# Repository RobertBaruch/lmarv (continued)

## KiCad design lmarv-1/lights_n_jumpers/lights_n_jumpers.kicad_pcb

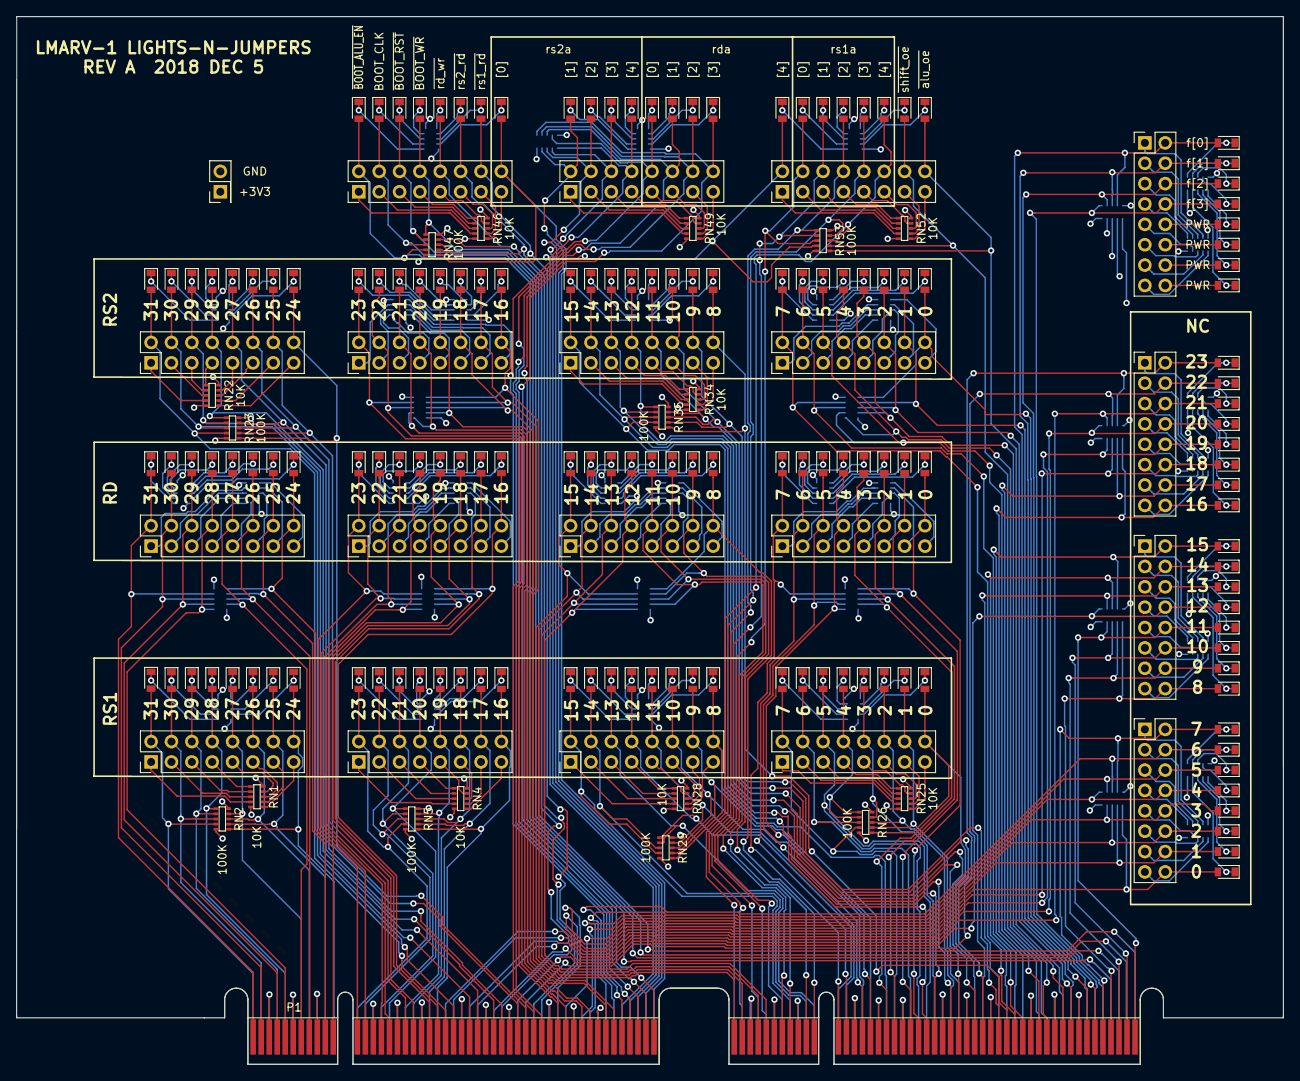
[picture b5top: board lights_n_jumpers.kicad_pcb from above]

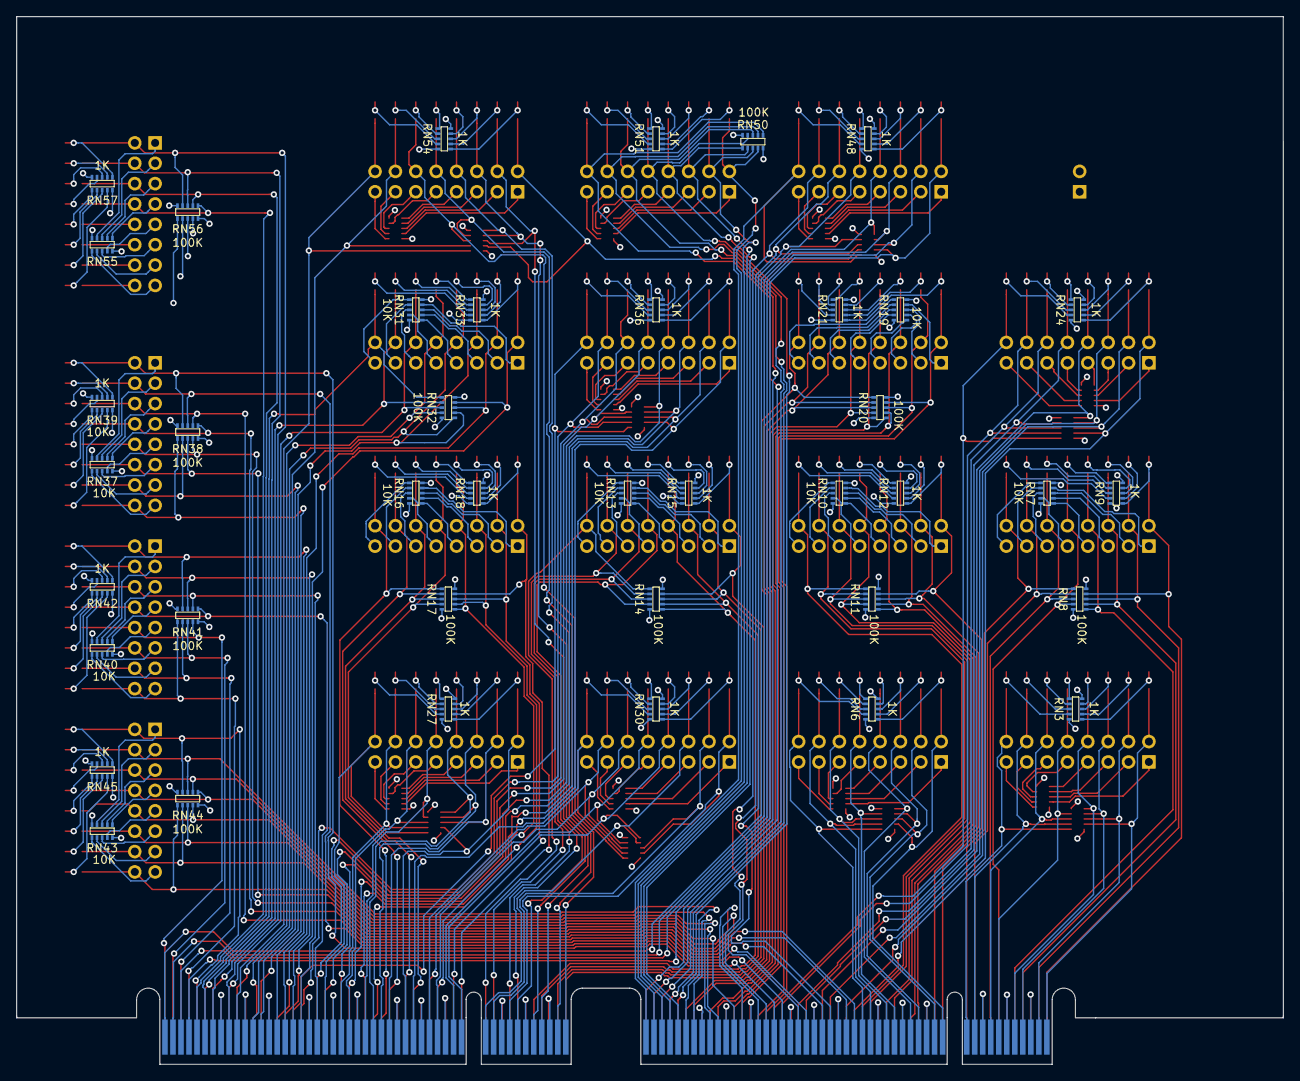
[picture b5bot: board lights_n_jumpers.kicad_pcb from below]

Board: 4 copper layers, 158.0 x 130.7 mm, 230 parts (40 on the bottom side), 454 nets.

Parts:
D1, D2, D3, D4, D5, D6, D7, D8, D9, D10, D11, D12, D13, D14, D15, D16, D17, D18, D19, D20, D21, D22, D23, D24, D25, D26, D27, D28, D29, D30, D31, D32, D33, D34, D35, D36, D37, D38, D39, D40, D41, D42, D43, D44, D45, D46, D47, D48, D49, D50, D51, D52, D53, D54, D55, D56, D57, D58, D59, D60, D61, D62, D63, D64, D65, D66, D67, D68, D69, D70, D71, D72, D73, D74, D75, D76, D77, D78, D79, D80, D81, D82, D83, D84, D85, D86, D87, D88, D89, D90, D91, D92, D93, D94, D95, D96, D97, D98, D99, D100, D101, D102, D103, D104, D105, D106, D107, D108, D109, D110, D111, D112, D113, D114, D115, D116, D117, D118, D119, D120, D121, D122, D123, D124, D125, D126, D127, D128, D129, D130, D131, D132, D133, D134, D135, D136, D137, D138, D139, D140, D141, D142, D143, D144, D145, D146, D147, D148, D149, D150, D151, D152: APTD2012LSURCK; D_0805_Wide
J1, J2, J3, J4, J5, J6, J7, J8, J10, J11, J12, J13, J14, J15, J16, J17, J18, J19, J20: Conn_02x08_Odd_Even; PinHeader_2x08_P2.54mm_Vertical
J9: Conn_01x02; PinHeader_2x01_P2.54mm_Vertical
P1: dual-pcie-cardedge_split; PCI-EXPRESS
RN1, RN4, RN7, RN10, RN13, RN16, RN19, RN22, RN25, RN28, RN31, RN34, RN37, RN40, RN43, RN46, RN49, RN52, RN55: 10k; CAY17
RN2, RN5, RN8, RN11, RN14, RN17, RN20, RN23, RN26, RN29, RN32, RN35, RN38, RN41, RN44, RN47, RN50, RN53, RN56: 100k; CAY17
RN3, RN6, RN9, RN12, RN15, RN18, RN21, RN24, RN27, RN30, RN33, RN36, RN39, RN42, RN45, RN48, RN51, RN54, RN57: 1k; CAY17

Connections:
+3V3: D145.2, D146.2, D147.2, D148.2, J9.1, J20.10, J20.12, J20.14, J20.16, P1.6, P1.17, P1.28, P1.39, P1.55, P1.66, P1.77, P1.88, P1.104, P1.115, P1.126, P1.137, P1.153, P1.164, P1.175, P1.186, RN1.5, RN1.10, RN4.5, RN4.10, RN7.5, RN7.10, RN10.5, RN10.10, RN13.5, RN13.10, RN16.5, RN16.10, RN19.5, RN19.10, RN22.5, RN22.10, RN25.5, RN25.10, RN28.5, RN28.10, RN31.5, RN31.10, RN34.5, RN34.10, RN37.5, RN37.10, RN40.5, RN40.10, RN43.5, RN43.10, RN46.5, RN46.10, RN49.5, RN49.10, RN52.5, RN52.10, RN55.5, RN55.10, RN56.1, RN56.2, RN56.3, RN56.4
/BOOT_CLK: D127.2, J17.4, P1.194, RN47.8
/f[0]: D152.2, J20.2, P1.188, RN56.9
/f[1]: D151.2, J20.4, P1.190, RN56.8
/f[2]: D150.2, J20.6, P1.191, RN56.7
/f[3]: D149.2, J20.8, P1.192, RN56.6
/nc0: D113.2, J16.16, P1.133, RN44.1
/nc1: D114.2, J16.14, P1.135, RN44.2
/nc2: D115.2, J16.12, P1.136, RN44.3
/nc3: D116.2, J16.10, P1.138, RN44.4
/nc4: D117.2, J16.8, P1.139, RN44.6
/nc5: D118.2, J16.6, P1.141, RN44.7
/nc6: D119.2, J16.4, P1.142, RN44.8
/nc7: D120.2, J16.2, P1.94, RN44.9
/nc8: D105.2, J15.16, P1.95, RN41.1
/nc9: D106.2, J15.14, P1.96, RN41.2
/nc10: D107.2, J15.12, P1.97, RN41.3
/nc11: D108.2, J15.10, P1.98, RN41.4
/nc12: D109.2, J15.8, P1.177, RN41.6
/nc13: D110.2, J15.6, P1.179, RN41.7
/nc14: D111.2, J15.4, P1.180, RN41.8
/nc15: D112.2, J15.2, P1.181, RN41.9
/nc16: D97.2, J14.16, P1.182, RN38.1
/nc17: D98.2, J14.14, P1.184, RN38.2
/nc18: D99.2, J14.12, P1.121, RN38.3
/nc19: D100.2, J14.10, P1.122, RN38.4
/nc20: D101.2, J14.8, P1.125, RN38.6
/nc21: D102.2, J14.6, P1.127, RN38.7
/nc22: D103.2, J14.4, P1.130, RN38.8
/nc23: D104.2, J14.2, P1.131, RN38.9
/rd[0]: D41.2, J6.16, P1.71, RN17.1
/rd[1]: D42.2, J6.14, P1.70, RN17.2
/rd[2]: D43.2, J6.12, P1.68, RN17.3
/rd[3]: D44.2, J6.10, P1.67, RN17.4
/rd[4]: D45.2, J6.8, P1.65, RN17.6
/rd[5]: D46.2, J6.6, P1.64, RN17.7
/rd[6]: D47.2, J6.4, P1.62, RN17.8
/rd[7]: D48.2, J6.2, P1.61, RN17.9
/rd[8]: D33.2, J5.16, P1.60, RN14.1
/rd[9]: D34.2, J5.14, P1.59, RN14.2
/rd[10]: D35.2, J5.12, P1.57, RN14.3
/rd[11]: D36.2, J5.10, P1.56, RN14.4
/rd[12]: D37.2, J5.8, P1.54, RN14.6
/rd[13]: D38.2, J5.6, P1.53, RN14.7
/rd[14]: D39.2, J5.4, P1.51, RN14.8
/rd[15]: D40.2, J5.2, P1.50, RN14.9
/rd[16]: D25.2, J4.16, P1.22, RN11.1
/rd[17]: D26.2, J4.14, P1.21, RN11.2
/rd[18]: D27.2, J4.12, P1.19, RN11.3
/rd[19]: D28.2, J4.10, P1.18, RN11.4
/rd[20]: D29.2, J4.8, P1.16, RN11.6
/rd[21]: D30.2, J4.6, P1.15, RN11.7
/rd[22]: D31.2, J4.4, P1.13, RN11.8
/rd[23]: D32.2, J4.2, P1.12, RN11.9
/rd[24]: D17.2, J3.16, P1.11, RN8.1
/rd[25]: D18.2, J3.14, P1.10, RN8.2
/rd[26]: D19.2, J3.12, P1.8, RN8.3
/rd[27]: D20.2, J3.10, P1.7, RN8.4
/rd[28]: D21.2, J3.8, P1.5, RN8.6
/rd[29]: D22.2, J3.6, P1.4, RN8.7
/rd[30]: D23.2, J3.4, P1.2, RN8.8
/rd[31]: D24.2, J3.2, P1.1, RN8.9
/rda[0]: D132.2, J18.10, P1.45, RN50.4
/rda[1]: D131.2, J18.12, P1.46, RN50.3
/rda[2]: D130.2, J18.14, P1.47, RN50.2
/rda[3]: D129.2, J18.16, P1.48, RN50.1
/rda[4]: D144.2, J19.2, P1.49, RN53.9
/rs1[0]: D65.2, J10.16, P1.176, RN26.1
/rs1[1]: D66.2, J10.14, P1.174, RN26.2
/rs1[2]: D67.2, J10.12, P1.173, RN26.3
/rs1[3]: D68.2, J10.10, P1.171, RN26.4
/rs1[4]: D69.2, J10.8, P1.170, RN26.6
/rs1[5]: D70.2, J10.6, P1.169, RN26.7
/rs1[6]: D71.2, J10.4, P1.168, RN26.8
/rs1[7]: D72.2, J10.2, P1.166, RN26.9
/rs1[8]: D73.2, J11.16, P1.165, RN29.1
/rs1[9]: D74.2, J11.14, P1.163, RN29.2
/rs1[10]: D75.2, J11.12, P1.162, RN29.3
/rs1[11]: D76.2, J11.10, P1.160, RN29.4
/rs1[12]: D77.2, J11.8, P1.159, RN29.6
/rs1[13]: D78.2, J11.6, P1.158, RN29.7
/rs1[14]: D79.2, J11.4, P1.157, RN29.8
/rs1[15]: D80.2, J11.2, P1.155, RN29.9
/rs1[16]: D9.2, J2.16, P1.120, RN5.1
/rs1[17]: D10.2, J2.14, P1.119, RN5.2
/rs1[18]: D11.2, J2.12, P1.117, RN5.3
/rs1[19]: D12.2, J2.10, P1.116, RN5.4
/rs1[20]: D13.2, J2.8, P1.114, RN5.6
/rs1[21]: D14.2, J2.6, P1.113, RN5.7
/rs1[22]: D15.2, J2.4, P1.111, RN5.8
/rs1[23]: D16.2, J2.2, P1.110, RN5.9
/rs1[24]: D1.2, J1.16, P1.109, RN2.1
/rs1[25]: D2.2, J1.14, P1.108, RN2.2
/rs1[26]: D3.2, J1.12, P1.106, RN2.3
/rs1[27]: D4.2, J1.10, P1.105, RN2.4
/rs1[28]: D5.2, J1.8, P1.103, RN2.6
/rs1[29]: D6.2, J1.6, P1.102, RN2.7
/rs1[30]: D7.2, J1.4, P1.100, RN2.8
/rs1[31]: D8.2, J1.2, P1.99, RN2.9
/rs1a[0]: D143.2, J19.4, P1.154, RN53.8
/rs1a[1]: D142.2, J19.6, P1.152, RN53.7
/rs1a[2]: D141.2, J19.8, P1.151, RN53.6
/rs1a[3]: D140.2, J19.10, P1.149, RN53.4
/rs1a[4]: D139.2, J19.12, P1.148, RN53.3
/rs2[0]: D81.2, J12.16, P1.93, RN32.1
/rs2[1]: D82.2, J12.14, P1.92, RN32.2
/rs2[2]: D83.2, J12.12, P1.90, RN32.3
/rs2[3]: D84.2, J12.10, P1.89, RN32.4
/rs2[4]: D85.2, J12.8, P1.87, RN32.6
/rs2[5]: D86.2, J12.6, P1.86, RN32.7
/rs2[6]: D87.2, J12.4, P1.84, RN32.8
/rs2[7]: D88.2, J12.2, P1.83, RN32.9
/rs2[8]: D89.2, J13.16, P1.82, RN35.1
/rs2[9]: D90.2, J13.14, P1.81, RN35.2
/rs2[10]: D91.2, J13.12, P1.79, RN35.3
/rs2[11]: D92.2, J13.10, P1.78, RN35.4
/rs2[12]: D93.2, J13.8, P1.76, RN35.6
/rs2[13]: D94.2, J13.6, P1.75, RN35.7
/rs2[14]: D95.2, J13.4, P1.73, RN35.8
/rs2[15]: D96.2, J13.2, P1.72, RN35.9
/rs2[16]: D49.2, J7.16, P1.44, RN20.1
/rs2[17]: D50.2, J7.14, P1.43, RN20.2
/rs2[18]: D51.2, J7.12, P1.41, RN20.3
/rs2[19]: D52.2, J7.10, P1.40, RN20.4
/rs2[20]: D53.2, J7.8, P1.38, RN20.6
/rs2[21]: D54.2, J7.6, P1.37, RN20.7
/rs2[22]: D55.2, J7.4, P1.35, RN20.8
/rs2[23]: D56.2, J7.2, P1.34, RN20.9
/rs2[24]: D57.2, J8.16, P1.33, RN23.1
/rs2[25]: D58.2, J8.14, P1.32, RN23.2
/rs2[26]: D59.2, J8.12, P1.30, RN23.3
/rs2[27]: D60.2, J8.10, P1.29, RN23.4
/rs2[28]: D61.2, J8.8, P1.27, RN23.6
/rs2[29]: D62.2, J8.6, P1.26, RN23.7
/rs2[30]: D63.2, J8.4, P1.24, RN23.8
/rs2[31]: D64.2, J8.2, P1.23, RN23.9
/rs2a[0]: D121.2, J17.16, P1.147, RN47.1
/rs2a[1]: D136.2, J18.2, P1.146, RN50.9
/rs2a[2]: D135.2, J18.4, P1.145, RN50.8
/rs2a[3]: D134.2, J18.6, P1.144, RN50.7
/rs2a[4]: D133.2, J18.8, P1.143, RN50.6
/~BOOT_ALU_EN: D128.2, J17.2, P1.193, RN47.9
/~BOOT_RST: D126.2, J17.6, P1.195, RN47.7
/~BOOT_WR: D125.2, J17.8, P1.196, RN47.6
/~alu_oe: D137.2, J19.16, P1.187, RN53.1
/~rd_wr: D124.2, J17.10, P1.124, RN47.4
/~rs1_rd: D122.2, J17.14, P1.132, RN47.2
/~rs2_rd: D123.2, J17.12, P1.128, RN47.3
/~shift_oe: D138.2, J19.14, P1.185, RN53.2
GNDREF: J9.2, P1.3, P1.9, P1.14, P1.20, P1.25, P1.31, P1.36, P1.42, P1.52, P1.58, P1.63, P1.69, P1.74, P1.80, P1.85, P1.91, P1.101, P1.107, P1.112, P1.118, P1.123, P1.129, P1.134, P1.140, P1.150, P1.156, P1.161, P1.167, P1.172, P1.178, P1.183, P1.189, RN2.5, RN2.10, RN3.5, RN3.10, RN5.5, RN5.10, RN6.5, RN6.10, RN8.5, RN8.10, RN9.5, RN9.10, RN11.5, RN11.10, RN12.5, RN12.10, RN14.5, RN14.10, RN15.5, RN15.10, RN17.5, RN17.10, RN18.5, RN18.10, RN20.5, RN20.10, RN21.5, RN21.10, RN23.5, RN23.10, RN24.5, RN24.10, RN26.5, RN26.10, RN27.5, RN27.10, RN29.5, RN29.10, RN30.5, RN30.10, RN32.5, RN32.10, RN33.5, RN33.10, RN35.5, RN35.10, RN36.5, RN36.10, RN38.5, RN38.10, RN39.5, RN39.10, RN41.5, RN41.10, RN42.5, RN42.10, RN44.5, RN44.10, RN45.5, RN45.10, RN47.5, RN47.10, RN48.5, RN48.10, RN50.5, RN50.10, RN51.5, RN51.10, RN53.5, RN53.10, RN54.5, RN54.10, RN56.5, RN56.10, RN57.5, RN57.10
unnamed: D1.1, RN3.4
unnamed: D2.1, RN3.3
unnamed: D3.1, RN3.2
unnamed: D4.1, RN3.1
unnamed: D5.1, RN3.9
unnamed: D6.1, RN3.8
unnamed: D7.1, RN3.7
unnamed: D8.1, RN3.6
unnamed: D9.1, RN6.4
unnamed: D10.1, RN6.3
unnamed: D11.1, RN6.2
unnamed: D12.1, RN6.1
unnamed: D13.1, RN6.9
unnamed: D14.1, RN6.8
unnamed: D15.1, RN6.7
unnamed: D16.1, RN6.6
unnamed: D17.1, RN9.4
unnamed: D18.1, RN9.3
unnamed: D19.1, RN9.2
unnamed: D20.1, RN9.1
unnamed: D21.1, RN9.9
unnamed: D22.1, RN9.8
unnamed: D23.1, RN9.7
unnamed: D24.1, RN9.6
unnamed: D25.1, RN12.4
unnamed: D26.1, RN12.3
unnamed: D27.1, RN12.2
unnamed: D28.1, RN12.1
unnamed: D29.1, RN12.9
unnamed: D30.1, RN12.8
unnamed: D31.1, RN12.7
unnamed: D32.1, RN12.6
unnamed: D33.1, RN15.4
unnamed: D34.1, RN15.3
unnamed: D35.1, RN15.2
unnamed: D36.1, RN15.1
unnamed: D37.1, RN15.9
unnamed: D38.1, RN15.8
unnamed: D39.1, RN15.7
unnamed: D40.1, RN15.6
unnamed: D41.1, RN18.4
unnamed: D42.1, RN18.3
unnamed: D43.1, RN18.2
unnamed: D44.1, RN18.1
unnamed: D45.1, RN18.9
unnamed: D46.1, RN18.8
unnamed: D47.1, RN18.7
unnamed: D48.1, RN18.6
unnamed: D49.1, RN21.4
unnamed: D50.1, RN21.3
unnamed: D51.1, RN21.2
unnamed: D52.1, RN21.1
unnamed: D53.1, RN21.9
unnamed: D54.1, RN21.8
unnamed: D55.1, RN21.7
unnamed: D56.1, RN21.6
unnamed: D57.1, RN24.4
unnamed: D58.1, RN24.3
unnamed: D59.1, RN24.2
unnamed: D60.1, RN24.1
unnamed: D61.1, RN24.9
unnamed: D62.1, RN24.8
unnamed: D63.1, RN24.7
unnamed: D64.1, RN24.6
unnamed: D65.1, RN27.4
unnamed: D66.1, RN27.3
unnamed: D67.1, RN27.2
unnamed: D68.1, RN27.1
unnamed: D69.1, RN27.9
unnamed: D70.1, RN27.8
unnamed: D71.1, RN27.7
unnamed: D72.1, RN27.6
unnamed: D73.1, RN30.4
unnamed: D74.1, RN30.3
unnamed: D75.1, RN30.2
unnamed: D76.1, RN30.1
unnamed: D77.1, RN30.9
unnamed: D78.1, RN30.8
unnamed: D79.1, RN30.7
unnamed: D80.1, RN30.6
unnamed: D81.1, RN33.4
unnamed: D82.1, RN33.3
unnamed: D83.1, RN33.2
unnamed: D84.1, RN33.1
unnamed: D85.1, RN33.9
unnamed: D86.1, RN33.8
unnamed: D87.1, RN33.7
unnamed: D88.1, RN33.6
unnamed: D89.1, RN36.4
unnamed: D90.1, RN36.3
unnamed: D91.1, RN36.2
unnamed: D92.1, RN36.1
unnamed: D93.1, RN36.9
unnamed: D94.1, RN36.8
unnamed: D95.1, RN36.7
unnamed: D96.1, RN36.6
unnamed: D97.1, RN39.4
unnamed: D98.1, RN39.3
unnamed: D99.1, RN39.2
unnamed: D100.1, RN39.1
unnamed: D101.1, RN39.9
unnamed: D102.1, RN39.8
unnamed: D103.1, RN39.7
unnamed: D104.1, RN39.6
unnamed: D105.1, RN42.4
unnamed: D106.1, RN42.3
unnamed: D107.1, RN42.2
unnamed: D108.1, RN42.1
unnamed: D109.1, RN42.9
unnamed: D110.1, RN42.8
unnamed: D111.1, RN42.7
unnamed: D112.1, RN42.6
unnamed: D113.1, RN45.4
unnamed: D114.1, RN45.3
unnamed: D115.1, RN45.2
unnamed: D116.1, RN45.1
unnamed: D117.1, RN45.9
unnamed: D118.1, RN45.8
unnamed: D119.1, RN45.7
unnamed: D120.1, RN45.6
unnamed: D121.1, RN48.4
unnamed: D122.1, RN48.3
unnamed: D123.1, RN48.2
unnamed: D124.1, RN48.1
unnamed: D125.1, RN48.9
unnamed: D126.1, RN48.8
unnamed: D127.1, RN48.7
unnamed: D128.1, RN48.6
unnamed: D129.1, RN51.4
unnamed: D130.1, RN51.3
unnamed: D131.1, RN51.2
unnamed: D132.1, RN51.1
unnamed: D133.1, RN51.9
unnamed: D134.1, RN51.8
unnamed: D135.1, RN51.7
unnamed: D136.1, RN51.6
unnamed: D137.1, RN54.4
unnamed: D138.1, RN54.3
unnamed: D139.1, RN54.2
unnamed: D140.1, RN54.1
unnamed: D141.1, RN54.9
unnamed: D142.1, RN54.8
unnamed: D143.1, RN54.7
unnamed: D144.1, RN54.6
unnamed: D145.1, RN57.4
unnamed: D146.1, RN57.3
unnamed: D147.1, RN57.2
unnamed: D148.1, RN57.1
unnamed: D149.1, RN57.9
unnamed: D150.1, RN57.8
unnamed: D151.1, RN57.7
unnamed: D152.1, RN57.6
unnamed: J1.1, RN1.9
unnamed: J1.3, RN1.8
unnamed: J1.5, RN1.7
unnamed: J1.7, RN1.6
unnamed: J1.9, RN1.4
unnamed: J1.11, RN1.3
unnamed: J1.13, RN1.2
unnamed: J1.15, RN1.1
unnamed: J2.1, RN4.9
unnamed: J2.3, RN4.8
unnamed: J2.5, RN4.7
unnamed: J2.7, RN4.6
unnamed: J2.9, RN4.4
unnamed: J2.11, RN4.3
unnamed: J2.13, RN4.2
unnamed: J2.15, RN4.1
unnamed: J3.1, RN7.9
unnamed: J3.3, RN7.8
unnamed: J3.5, RN7.7
unnamed: J3.7, RN7.6
unnamed: J3.9, RN7.4
unnamed: J3.11, RN7.3
unnamed: J3.13, RN7.2
unnamed: J3.15, RN7.1
unnamed: J4.1, RN10.9
unnamed: J4.3, RN10.8
unnamed: J4.5, RN10.7
unnamed: J4.7, RN10.6
unnamed: J4.9, RN10.4
unnamed: J4.11, RN10.3
unnamed: J4.13, RN10.2
unnamed: J4.15, RN10.1
unnamed: J5.1, RN13.9
unnamed: J5.3, RN13.8
unnamed: J5.5, RN13.7
unnamed: J5.7, RN13.6
unnamed: J5.9, RN13.4
unnamed: J5.11, RN13.3
unnamed: J5.13, RN13.2
unnamed: J5.15, RN13.1
unnamed: J6.1, RN16.9
unnamed: J6.3, RN16.8
unnamed: J6.5, RN16.7
unnamed: J6.7, RN16.6
unnamed: J6.9, RN16.4
unnamed: J6.11, RN16.3
unnamed: J6.13, RN16.2
unnamed: J6.15, RN16.1
unnamed: J7.1, RN19.9
unnamed: J7.3, RN19.8
unnamed: J7.5, RN19.7
unnamed: J7.7, RN19.6
unnamed: J7.9, RN19.4
unnamed: J7.11, RN19.3
unnamed: J7.13, RN19.2
unnamed: J7.15, RN19.1
unnamed: J8.1, RN22.9
unnamed: J8.3, RN22.8
unnamed: J8.5, RN22.7
unnamed: J8.7, RN22.6
unnamed: J8.9, RN22.4
unnamed: J8.11, RN22.3
unnamed: J8.13, RN22.2
unnamed: J8.15, RN22.1
unnamed: J10.1, RN25.9
unnamed: J10.3, RN25.8
unnamed: J10.5, RN25.7
unnamed: J10.7, RN25.6
unnamed: J10.9, RN25.4
unnamed: J10.11, RN25.3
unnamed: J10.13, RN25.2
unnamed: J10.15, RN25.1
unnamed: J11.1, RN28.9
unnamed: J11.3, RN28.8
unnamed: J11.5, RN28.7
unnamed: J11.7, RN28.6
unnamed: J11.9, RN28.4
unnamed: J11.11, RN28.3
unnamed: J11.13, RN28.2
unnamed: J11.15, RN28.1
unnamed: J12.1, RN31.9
unnamed: J12.3, RN31.8
unnamed: J12.5, RN31.7
unnamed: J12.7, RN31.6
unnamed: J12.9, RN31.4
unnamed: J12.11, RN31.3
unnamed: J12.13, RN31.2
unnamed: J12.15, RN31.1
unnamed: J13.1, RN34.9
unnamed: J13.3, RN34.8
unnamed: J13.5, RN34.7
unnamed: J13.7, RN34.6
unnamed: J13.9, RN34.4
unnamed: J13.11, RN34.3
unnamed: J13.13, RN34.2
unnamed: J13.15, RN34.1
unnamed: J14.1, RN37.9
unnamed: J14.3, RN37.8
unnamed: J14.5, RN37.7
unnamed: J14.7, RN37.6
unnamed: J14.9, RN37.4
unnamed: J14.11, RN37.3
unnamed: J14.13, RN37.2
unnamed: J14.15, RN37.1
unnamed: J15.1, RN40.9
unnamed: J15.3, RN40.8
unnamed: J15.5, RN40.7
unnamed: J15.7, RN40.6
unnamed: J15.9, RN40.4
unnamed: J15.11, RN40.3
unnamed: J15.13, RN40.2
unnamed: J15.15, RN40.1
unnamed: J16.1, RN43.9
unnamed: J16.3, RN43.8
unnamed: J16.5, RN43.7
unnamed: J16.7, RN43.6
unnamed: J16.9, RN43.4
unnamed: J16.11, RN43.3
unnamed: J16.13, RN43.2
unnamed: J16.15, RN43.1
unnamed: J17.1, RN46.9
unnamed: J17.3, RN46.8
unnamed: J17.5, RN46.7
unnamed: J17.7, RN46.6
unnamed: J17.9, RN46.4
unnamed: J17.11, RN46.3
unnamed: J17.13, RN46.2
unnamed: J17.15, RN46.1
unnamed: J18.1, RN49.9
unnamed: J18.3, RN49.8
unnamed: J18.5, RN49.7
unnamed: J18.7, RN49.6
unnamed: J18.9, RN49.4
unnamed: J18.11, RN49.3
unnamed: J18.13, RN49.2
unnamed: J18.15, RN49.1
unnamed: J19.1, RN52.9
unnamed: J19.3, RN52.8
unnamed: J19.5, RN52.7
unnamed: J19.7, RN52.6
unnamed: J19.9, RN52.4
unnamed: J19.11, RN52.3
unnamed: J19.13, RN52.2
unnamed: J19.15, RN52.1
unnamed: J20.1, RN55.9
unnamed: J20.3, RN55.8
unnamed: J20.5, RN55.7
unnamed: J20.7, RN55.6
unnamed: J20.9, RN55.4
unnamed: J20.11, RN55.3
unnamed: J20.13, RN55.2
unnamed: J20.15, RN55.1

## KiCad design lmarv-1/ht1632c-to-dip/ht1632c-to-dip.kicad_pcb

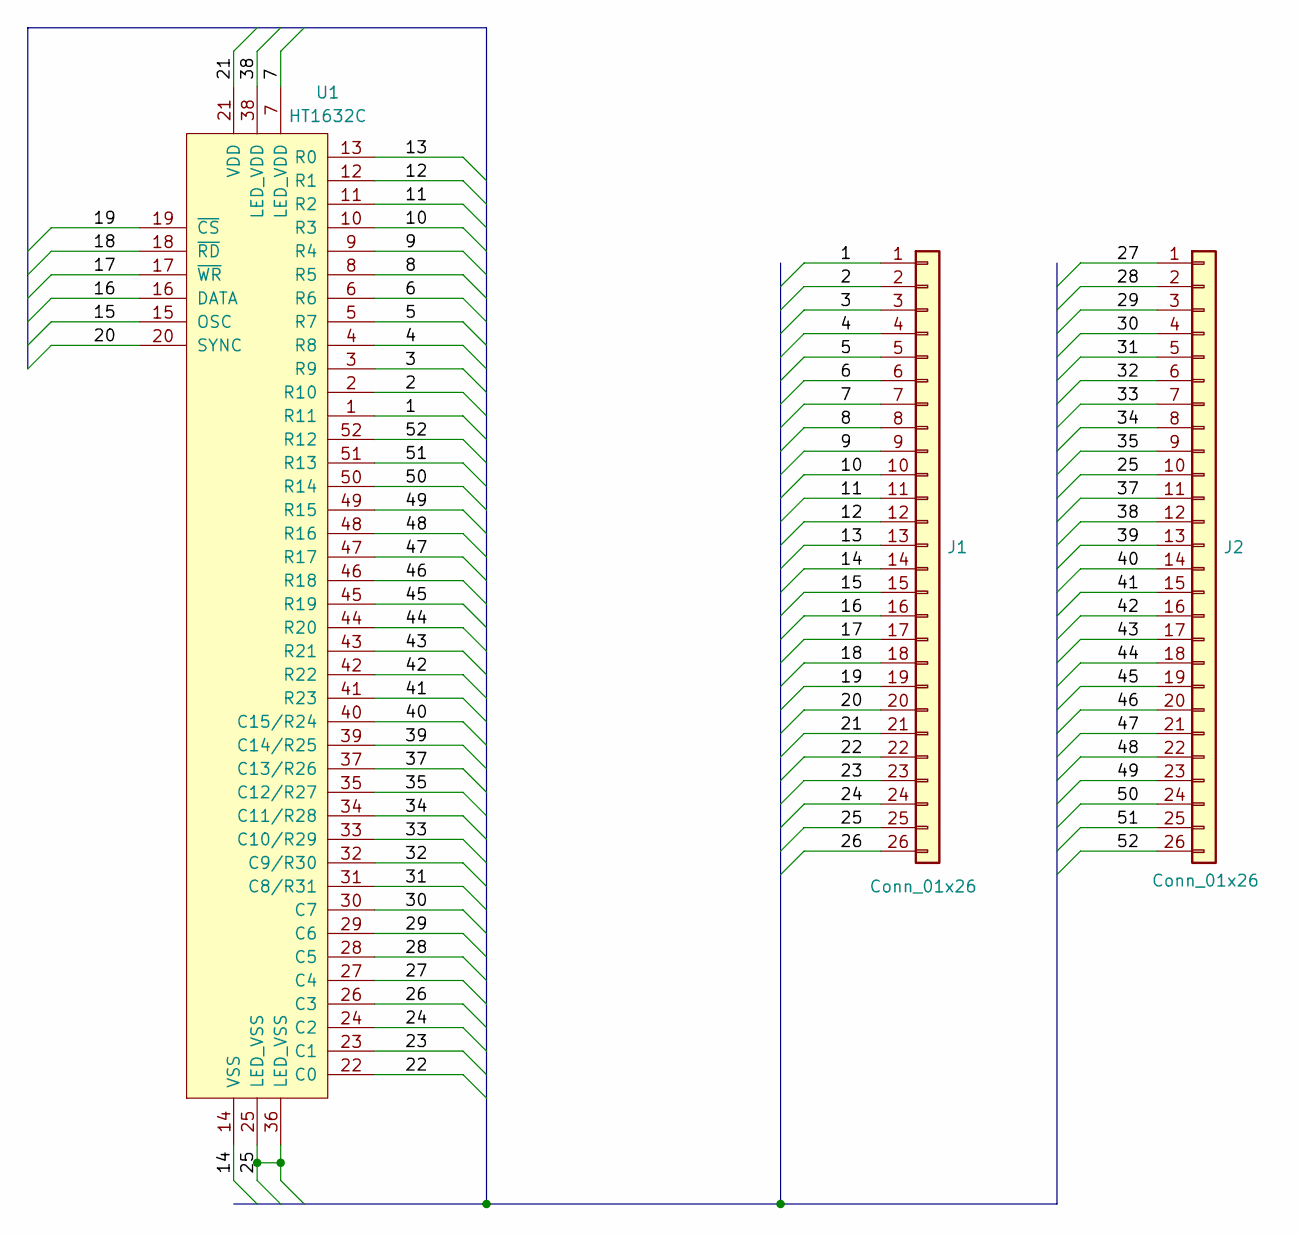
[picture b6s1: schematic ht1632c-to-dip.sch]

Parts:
J1, J2: Conn_01x26; PinHeader_1x26_P2.54mm_Vertical
U1: HT1632C; QFP-52_14x14_Pitch1mm

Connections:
/1: J1.1, U1.1 (R11)
/2: J1.2, U1.2 (R10)
/3: J1.3, U1.3 (R9)
/4: J1.4, U1.4 (R8)
/5: J1.5, U1.5 (R7)
/6: J1.6, U1.6 (R6)
/7: J1.7, U1.7 (LED_VDD)
/8: J1.8, U1.8 (R5)
/9: J1.9, U1.9 (R4)
/10: J1.10, U1.10 (R3)
/11: J1.11, U1.11 (R2)
/12: J1.12, U1.12 (R1)
/13: J1.13, U1.13 (R0)
/14: J1.14, U1.14 (VSS)
/15: J1.15, U1.15 (OSC)
/16: J1.16, U1.16 (DATA)
/17: J1.17, U1.17 (~WR)
/18: J1.18, U1.18 (~RD)
/19: J1.19, U1.19 (~CS)
/20: J1.20, U1.20 (SYNC)
/21: J1.21, U1.21 (VDD)
/22: J1.22, U1.22 (C0)
/23: J1.23, U1.23 (C1)
/24: J1.24, U1.24 (C2)
/25: J1.25, J2.10, U1.25 (LED_VSS), U1.36 (LED_VSS)
/26: J1.26, U1.26 (C3)
/27: J2.1, U1.27 (C4)
/28: J2.2, U1.28 (C5)
/29: J2.3, U1.29 (C6)
/30: J2.4, U1.30 (C7)
/31: J2.5, U1.31 (C8/R31)
/32: J2.6, U1.32 (C9/R30)
/33: J2.7, U1.33 (C10/R29)
/34: J2.8, U1.34 (C11/R28)
/35: J2.9, U1.35 (C12/R27)
/37: J2.11, U1.37 (C13/R26)
/38: J2.12, U1.38 (LED_VDD)
/39: J2.13, U1.39 (C14/R25)
/40: J2.14, U1.40 (C15/R24)
/41: J2.15, U1.41 (R23)
/42: J2.16, U1.42 (R22)
/43: J2.17, U1.43 (R21)
/44: J2.18, U1.44 (R20)
/45: J2.19, U1.45 (R19)
/46: J2.20, U1.46 (R18)
/47: J2.21, U1.47 (R17)
/48: J2.22, U1.48 (R16)
/49: J2.23, U1.49 (R15)
/50: J2.24, U1.50 (R14)
/51: J2.25, U1.51 (R13)
/52: J2.26, U1.52 (R12)

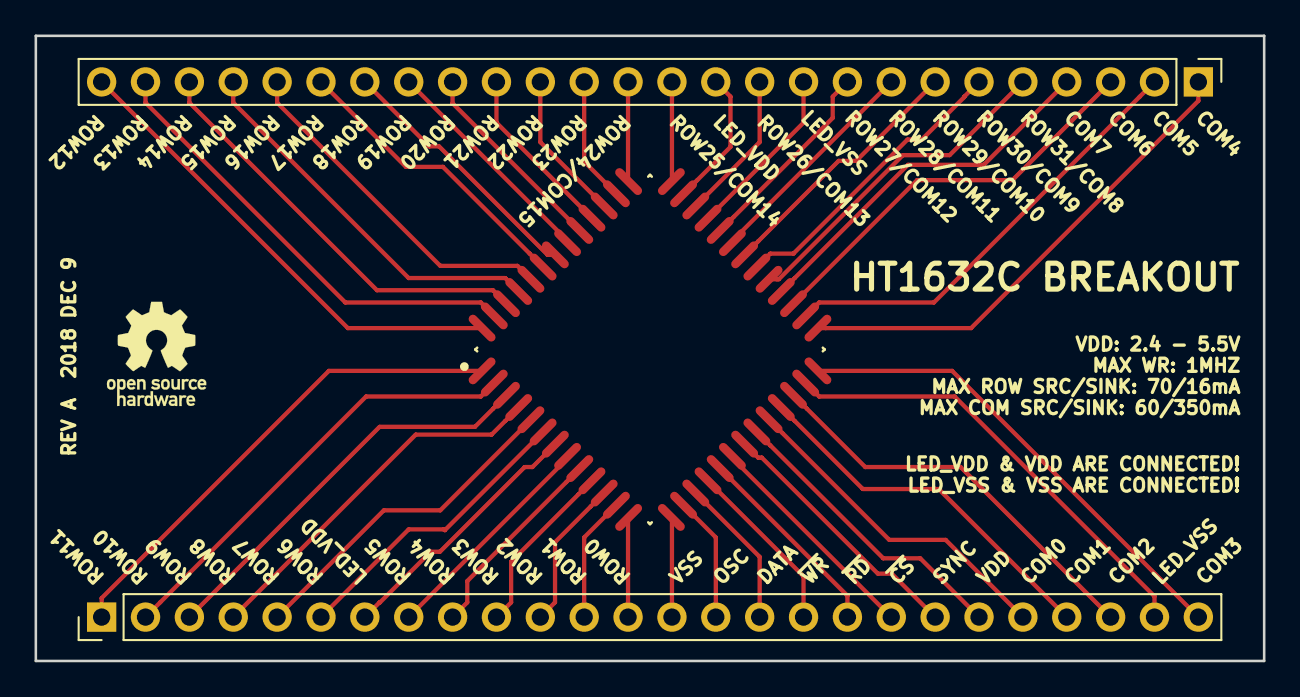
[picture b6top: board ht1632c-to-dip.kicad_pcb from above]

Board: 2 copper layers, 71.1 x 36.2 mm, 3 parts (0 on the bottom side), 51 nets.

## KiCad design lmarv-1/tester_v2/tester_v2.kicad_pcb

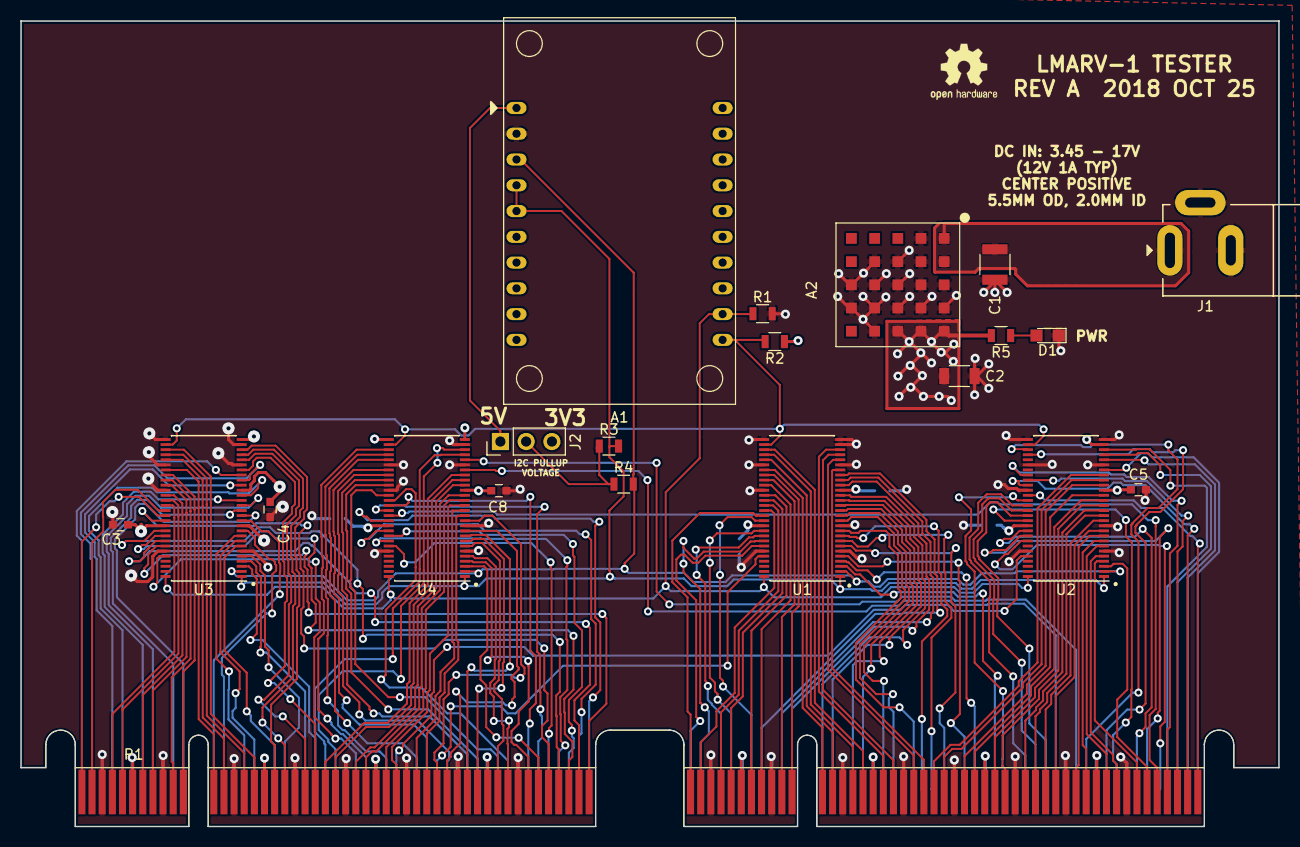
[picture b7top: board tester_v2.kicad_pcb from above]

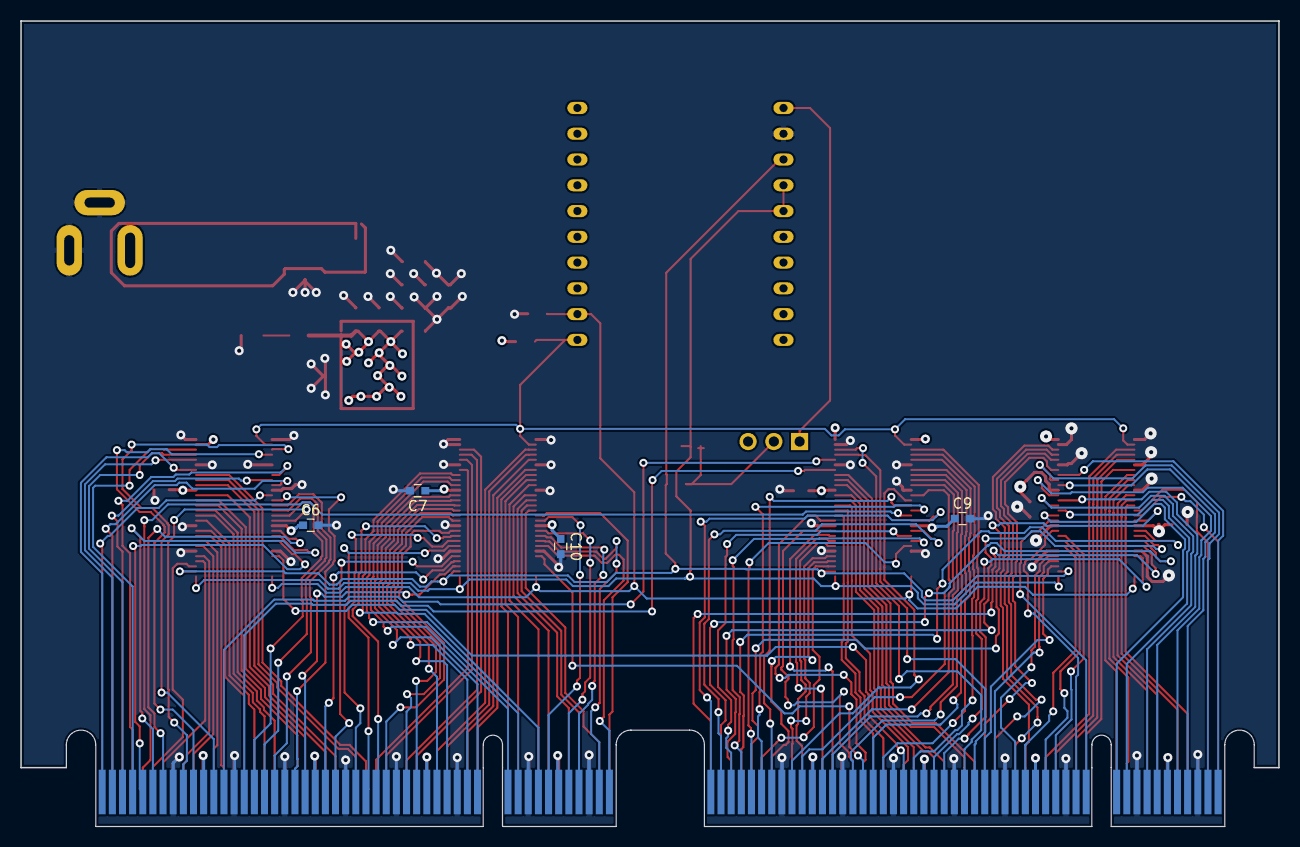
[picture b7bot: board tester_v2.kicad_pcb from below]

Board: 4 copper layers, 124.0 x 79.4 mm, 25 parts (4 on the bottom side), 158 nets.

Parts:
A1: FT232H_BREAKOUT; ADAFRUIT-FT232H
A2: RPM3.3-3.0; LGA-25_12.19x12.19mm_Layout5x5_P2.29mm_Pad1.0mm
C1: 10u 25v; C_1210
C2: 22u 10v; C_1206
C3, C4, C5, C6, C7, C8, C9, C10: 100n; C_0603
D1: LED; LED_0805
J1: Barrel_Jack; PWRJACK-3_14.4x9.0mm_P4.7mm+6.0mm
J2: Conn_01x03; Pin_Header_Straight_1x03_Pitch2.54mm
P1: dual-pcie-cardedge_split; PCI-EXPRESS
R1, R2, R3, R4: 4k7; R_0805
R5: 220R; R_0805
U1, U2, U3, U4: PCA9698DDG; TSSOP-56_6.1x14mm_Pitch0.5mm

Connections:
+3V3: A2.A5, A2.B5, A2.C5, C2.1, C3.1, C4.1, C5.1, C6.1, C7.1, C8.1, C9.1, C10.1, J2.3, P1.6, P1.17, P1.28, P1.39, P1.55, P1.66, P1.77, P1.88, P1.104, P1.115, P1.126, P1.137, P1.153, P1.164, P1.175, P1.186, R2.1, R5.2, U1.18, U1.46, U2.18, U2.27, U2.46, U3.18, U3.28, U3.46, U4.18, U4.28, U4.29, U4.46
/5V: A1.1, J2.1
/BOOT_CLK: P1.194, U2.25
/I2C_PU: J2.2, R3.1, R4.1
/PWR_LED: D1.2, R5.1
/SCL: A1.3, R4.2, U1.2, U2.2, U3.2, U4.2
/SDA: A1.4, A1.5, R3.2, U1.1, U2.1, U3.1, U4.1
/VIN: A2.A1, A2.A2, C1.1, J1.1
/f[0]: P1.188, U2.45
/f[1]: P1.190, U2.47
/f[2]: P1.191, U2.48
/f[3]: P1.192, U2.49
/nc0: P1.133, U4.36
/nc1: P1.135, U4.37
/nc2: P1.136, U4.38
/nc3: P1.138, U4.40
/nc4: P1.139, U4.41
/nc5: P1.141, U4.42
/nc6: P1.142, U4.43
/nc7: P1.94, U4.44
/nc8: P1.95, U2.36
/nc9: P1.96, U2.37
/nc10: P1.97, U2.38
/nc11: P1.98, U2.40
/nc12: P1.177, U2.41
/nc13: P1.179, U2.42
/nc14: P1.180, U2.43
/nc15: P1.181, U2.44
/nc16: P1.182, U4.22
/nc17: P1.184, U4.24
/nc18: P1.121, U4.25
/nc19: P1.122, U4.26
/nc20: P1.125, U4.31
/nc21: P1.127, U4.32
/nc22: P1.130, U4.33
/nc23: P1.131, U4.35
/rd[0]: P1.71, U1.22
/rd[1]: P1.70, U1.24
/rd[2]: P1.68, U1.25
/rd[3]: P1.67, U1.26
/rd[4]: P1.65, U1.31
/rd[5]: P1.64, U1.32
/rd[6]: P1.62, U1.33
/rd[7]: P1.61, U1.35
/rd[8]: P1.60, U1.36
/rd[9]: P1.59, U1.37
/rd[10]: P1.57, U1.38
/rd[11]: P1.56, U1.40
/rd[12]: P1.54, U1.41
/rd[13]: P1.53, U1.42
/rd[14]: P1.51, U1.43
/rd[15]: P1.50, U1.44
/rd[16]: P1.22, U3.22
/rd[17]: P1.21, U3.24
/rd[18]: P1.19, U3.25
/rd[19]: P1.18, U3.26
/rd[20]: P1.16, U3.31
/rd[21]: P1.15, U3.32
/rd[22]: P1.13, U3.33
/rd[23]: P1.12, U3.35
/rd[24]: P1.11, U3.36
/rd[25]: P1.10, U3.37
/rd[26]: P1.8, U3.38
/rd[27]: P1.7, U3.40
/rd[28]: P1.5, U3.41
/rd[29]: P1.4, U3.42
/rd[30]: P1.2, U3.43
/rd[31]: P1.1, U3.44
/rda[0]: P1.45, U3.45
/rda[1]: P1.46, U3.47
/rda[2]: P1.47, U3.48
/rda[3]: P1.48, U3.49
/rda[4]: P1.49, U3.50
/rs1[0]: P1.176, U1.3
/rs1[1]: P1.174, U1.4
/rs1[2]: P1.173, U1.5
/rs1[3]: P1.171, U1.7
/rs1[4]: P1.170, U1.8
/rs1[5]: P1.169, U1.9
/rs1[6]: P1.168, U1.10
/rs1[7]: P1.166, U1.12
/rs1[8]: P1.165, U1.13
/rs1[9]: P1.163, U1.14
/rs1[10]: P1.162, U1.15
/rs1[11]: P1.160, U1.16
/rs1[12]: P1.159, U1.17
/rs1[13]: P1.158, U1.19
/rs1[14]: P1.157, U1.20
/rs1[15]: P1.155, U1.21
/rs1[16]: P1.120, U3.3
/rs1[17]: P1.119, U3.4
/rs1[18]: P1.117, U3.5
/rs1[19]: P1.116, U3.7
/rs1[20]: P1.114, U3.8
/rs1[21]: P1.113, U3.9
/rs1[22]: P1.111, U3.10
/rs1[23]: P1.110, U3.12
/rs1[24]: P1.109, U3.13
/rs1[25]: P1.108, U3.14
/rs1[26]: P1.106, U3.15
/rs1[27]: P1.105, U3.16
/rs1[28]: P1.103, U3.17
/rs1[29]: P1.102, U3.19
/rs1[30]: P1.100, U3.20
/rs1[31]: P1.99, U3.21
/rs1a[0]: P1.154, U1.45
/rs1a[1]: P1.152, U1.47
/rs1a[2]: P1.151, U1.48
/rs1a[3]: P1.149, U1.49
/rs1a[4]: P1.148, U1.50
/rs2[0]: P1.93, U2.3
/rs2[1]: P1.92, U2.4
/rs2[2]: P1.90, U2.5
/rs2[3]: P1.89, U2.7
/rs2[4]: P1.87, U2.8
/rs2[5]: P1.86, U2.9
/rs2[6]: P1.84, U2.10
/rs2[7]: P1.83, U2.12
/rs2[8]: P1.82, U2.13
/rs2[9]: P1.81, U2.14
/rs2[10]: P1.79, U2.15
/rs2[11]: P1.78, U2.16
/rs2[12]: P1.76, U2.17
/rs2[13]: P1.75, U2.19
/rs2[14]: P1.73, U2.20
/rs2[15]: P1.72, U2.21
/rs2[16]: P1.44, U4.3
/rs2[17]: P1.43, U4.4
/rs2[18]: P1.41, U4.5
/rs2[19]: P1.40, U4.7
/rs2[20]: P1.38, U4.8
/rs2[21]: P1.37, U4.9
/rs2[22]: P1.35, U4.10
/rs2[23]: P1.34, U4.12
/rs2[24]: P1.33, U4.13
/rs2[25]: P1.32, U4.14
/rs2[26]: P1.30, U4.15
/rs2[27]: P1.29, U4.16
/rs2[28]: P1.27, U4.17
/rs2[29]: P1.26, U4.19
/rs2[30]: P1.24, U4.20
/rs2[31]: P1.23, U4.21
/rs2a[0]: P1.147, U4.45
/rs2a[1]: P1.146, U4.47
/rs2a[2]: P1.145, U4.48
/rs2a[3]: P1.144, U4.49
/rs2a[4]: P1.143, U4.50
/~BOOT_ALU_EN: P1.193, U2.26
/~BOOT_RST: P1.195, U2.24
/~BOOT_WR: P1.196, U2.22
/~OE: A1.11, R2.2, U1.30, U2.30, U3.30, U4.30
/~RESET: A1.12, R1.1, U1.56, U2.56, U3.56, U4.56
/~alu_oe: P1.187, U2.32
/~rd_wr: P1.124, U3.52
/~rs1_rd: P1.132, U1.52
/~rs2_rd: P1.128, U2.52
/~shift_oe: P1.185, U2.31
GNDREF: A1.2, A2.A3, A2.A4, A2.B1, A2.B2, A2.B3, A2.B4, A2.C2, A2.C3, A2.C4, A2.D2, A2.D3, A2.D4, A2.D5, A2.E3, A2.E4, C1.2, C2.2, C3.2, C4.2, C5.2, C6.2, C7.2, C8.2, C9.2, C10.2, D1.1, J1.2, J1.3, P1.3, P1.9, P1.14, P1.20, P1.25, P1.31, P1.36, P1.42, P1.52, P1.58, P1.63, P1.69, P1.74, P1.80, P1.85, P1.91, P1.101, P1.107, P1.112, P1.118, P1.123, P1.129, P1.134, P1.140, P1.150, P1.156, P1.161, P1.167, P1.172, P1.178, P1.183, P1.189, R1.2, U1.6, U1.11, U1.23, U1.27, U1.28, U1.29, U1.34, U1.39, U1.51, U2.6, U2.11, U2.23, U2.28, U2.29, U2.34, U2.39, U2.51, U3.6, U3.11, U3.23, U3.27, U3.29, U3.34, U3.39, U3.51, U4.6, U4.11, U4.23, U4.27, U4.34, U4.39, U4.51
